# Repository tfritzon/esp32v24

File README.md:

# esp32v24
ESP32-based V.24 plug

ESP32V24 is an ESP32 with a RS-232, or V.24, interface that fits into a 9-pin D-Sub
backshell. The idea with it is to be able to comfortably use a device equiped with
only a serial port over a network. Possible uses are as a terminal server for a
retro computer, a network CAT interface for a ham radio or to interface with an
old PLL that only has serial interfaces.

So far, this is a project in it's infancy, but possible features might be:

* Application framework that includes:
  * Connecting to a Wifi network
  * Webserver for configuration
  * RESTful service for runtime control
  * Error handling
  * Zeroconf with configurable name, to be addressable as _name_.local
* OTA updates
* Application API to make it simple to develop a domain specific application.
* AT command parser to be used from within the connected device

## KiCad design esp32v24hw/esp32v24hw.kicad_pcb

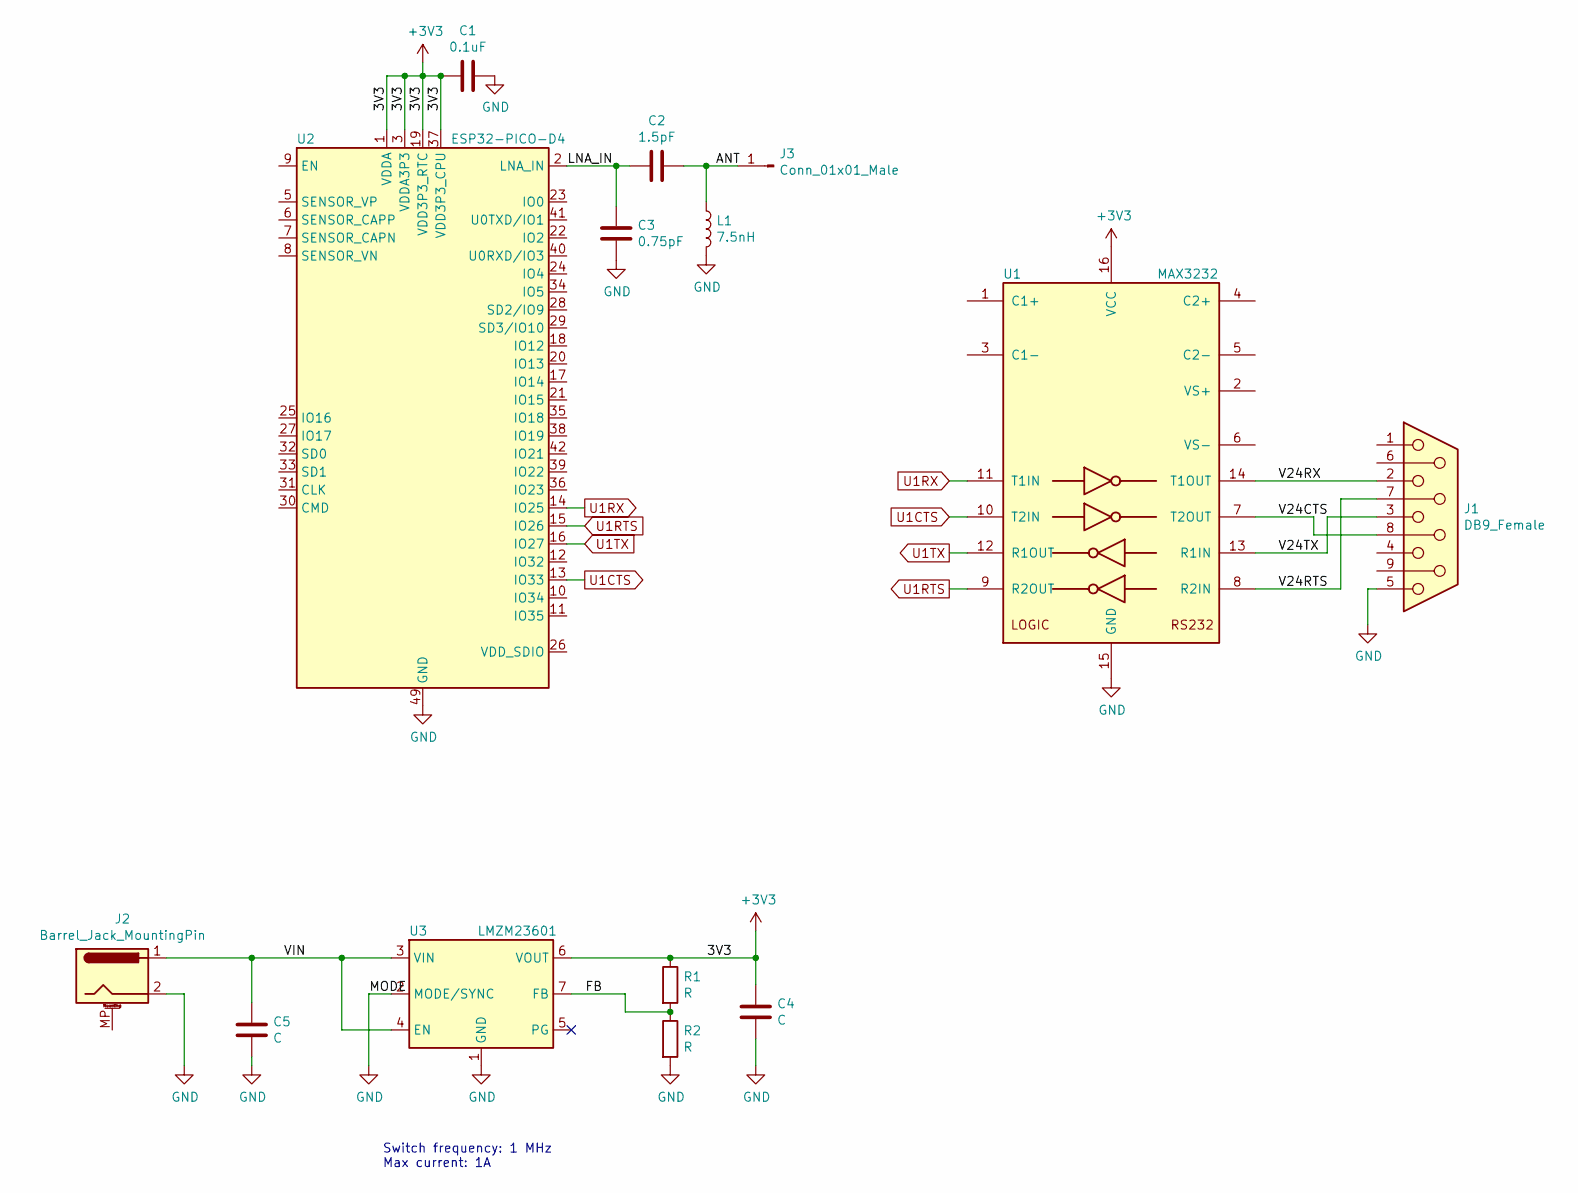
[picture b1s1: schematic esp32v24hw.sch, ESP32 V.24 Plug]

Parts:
C1: 0.1uF; C_0402_1005Metric
C2: 1.5pF; C_0402_1005Metric
C3: 0.75pF; C_0402_1005Metric
C4, C5: C; C_0402_1005Metric
J1: DB9_Female; DSUB-9_Female_EdgeMount_P2.77mm
J2: Barrel_Jack_MountingPin; BarrelJack_CUI_PJ-102AH_Horizontal
J3: Conn_01x01_Male; PinHeader_1x01_P2.54mm_Vertical
L1: 7.5nH; L_0402_1005Metric
R1, R2: R; R_0402_1005Metric
U1: MAX3232; TQFN-16-1EP_5x5mm_P0.8mm_EP3.1x3.1mm
U2: ESP32-PICO-D4; QFN-48-1EP_7x7mm_P0.5mm_EP5.3x5.3mm
U3: LMZM23601; Texas_SIL0010A_MicroSiP-10-1EP_3.8x3mm_P0.6mm_EP0.7x2.9mm_T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

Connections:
+3V3: C1.2, C4.1, R1.1, U1.16 (VCC), U2.1 (VDDA), U2.3 (VDDA3P3), U2.4 (VDDA3P3), U2.19 (VDD3P3_RTC), U2.37 (VDD3P3_CPU), U2.38 (IO19), U2.43 (VDDA), U2.46 (VDDA), U3.6 (VOUT)
/ANT: C2.1, J3.1, L1.1; also elsewhere on the board
/FB: R1.2, R2.1, U3.7 (FB)
/LNA_IN: C2.2, C3.1, U2.2 (LNA_IN)
/V24CTS: J1.8, U1.7 (T2OUT)
/V24RTS: J1.7, U1.8 (R2IN)
/V24RX: J1.2, U1.14 (T1OUT)
/V24TX: J1.3, U1.13 (R1IN)
/VIN: C5.1, J2.1, U3.3 (VIN), U3.4 (EN)
GND: C1.1, C3.2, C4.2, C5.2, J1.5, J2.2, L1.2, R2.2, U1.15 (GND), U1.17, U2.49 (GND), U3.1 (GND), U3.2 (MODE/SYNC), U3.11 (GND)
U1CTS: U1.10 (T2IN), U2.13 (IO33)
U1RTS: U1.9 (R2OUT), U2.15 (IO26)
U1RX: U1.11 (T1IN), U2.14 (IO25)
U1TX: U1.12 (R1OUT), U2.16 (IO27)

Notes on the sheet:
Switch frequency: 1 MHz Max current: 1A

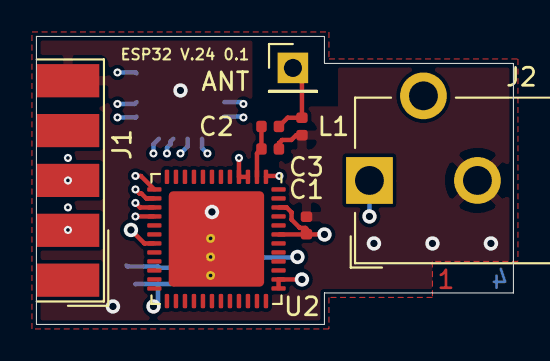
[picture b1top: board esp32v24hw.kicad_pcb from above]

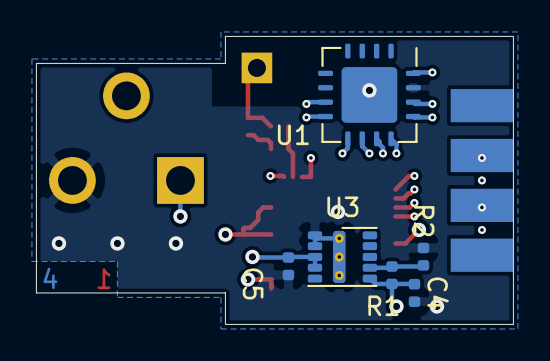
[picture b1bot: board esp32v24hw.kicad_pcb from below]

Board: 4 copper layers, 26.5 x 16.0 mm, 14 parts (6 on the bottom side), 14 nets.

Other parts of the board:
ANT: Conn_01x01_Male; PinHeader_1x01_P2.54mm_Vertical

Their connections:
/ANT: ANT.1; also elsewhere on the board

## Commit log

2020-07-20 First stab at the HW.
2020-07-20 Added some info in README
2020-07-20 Added schematics and board pdfs.
